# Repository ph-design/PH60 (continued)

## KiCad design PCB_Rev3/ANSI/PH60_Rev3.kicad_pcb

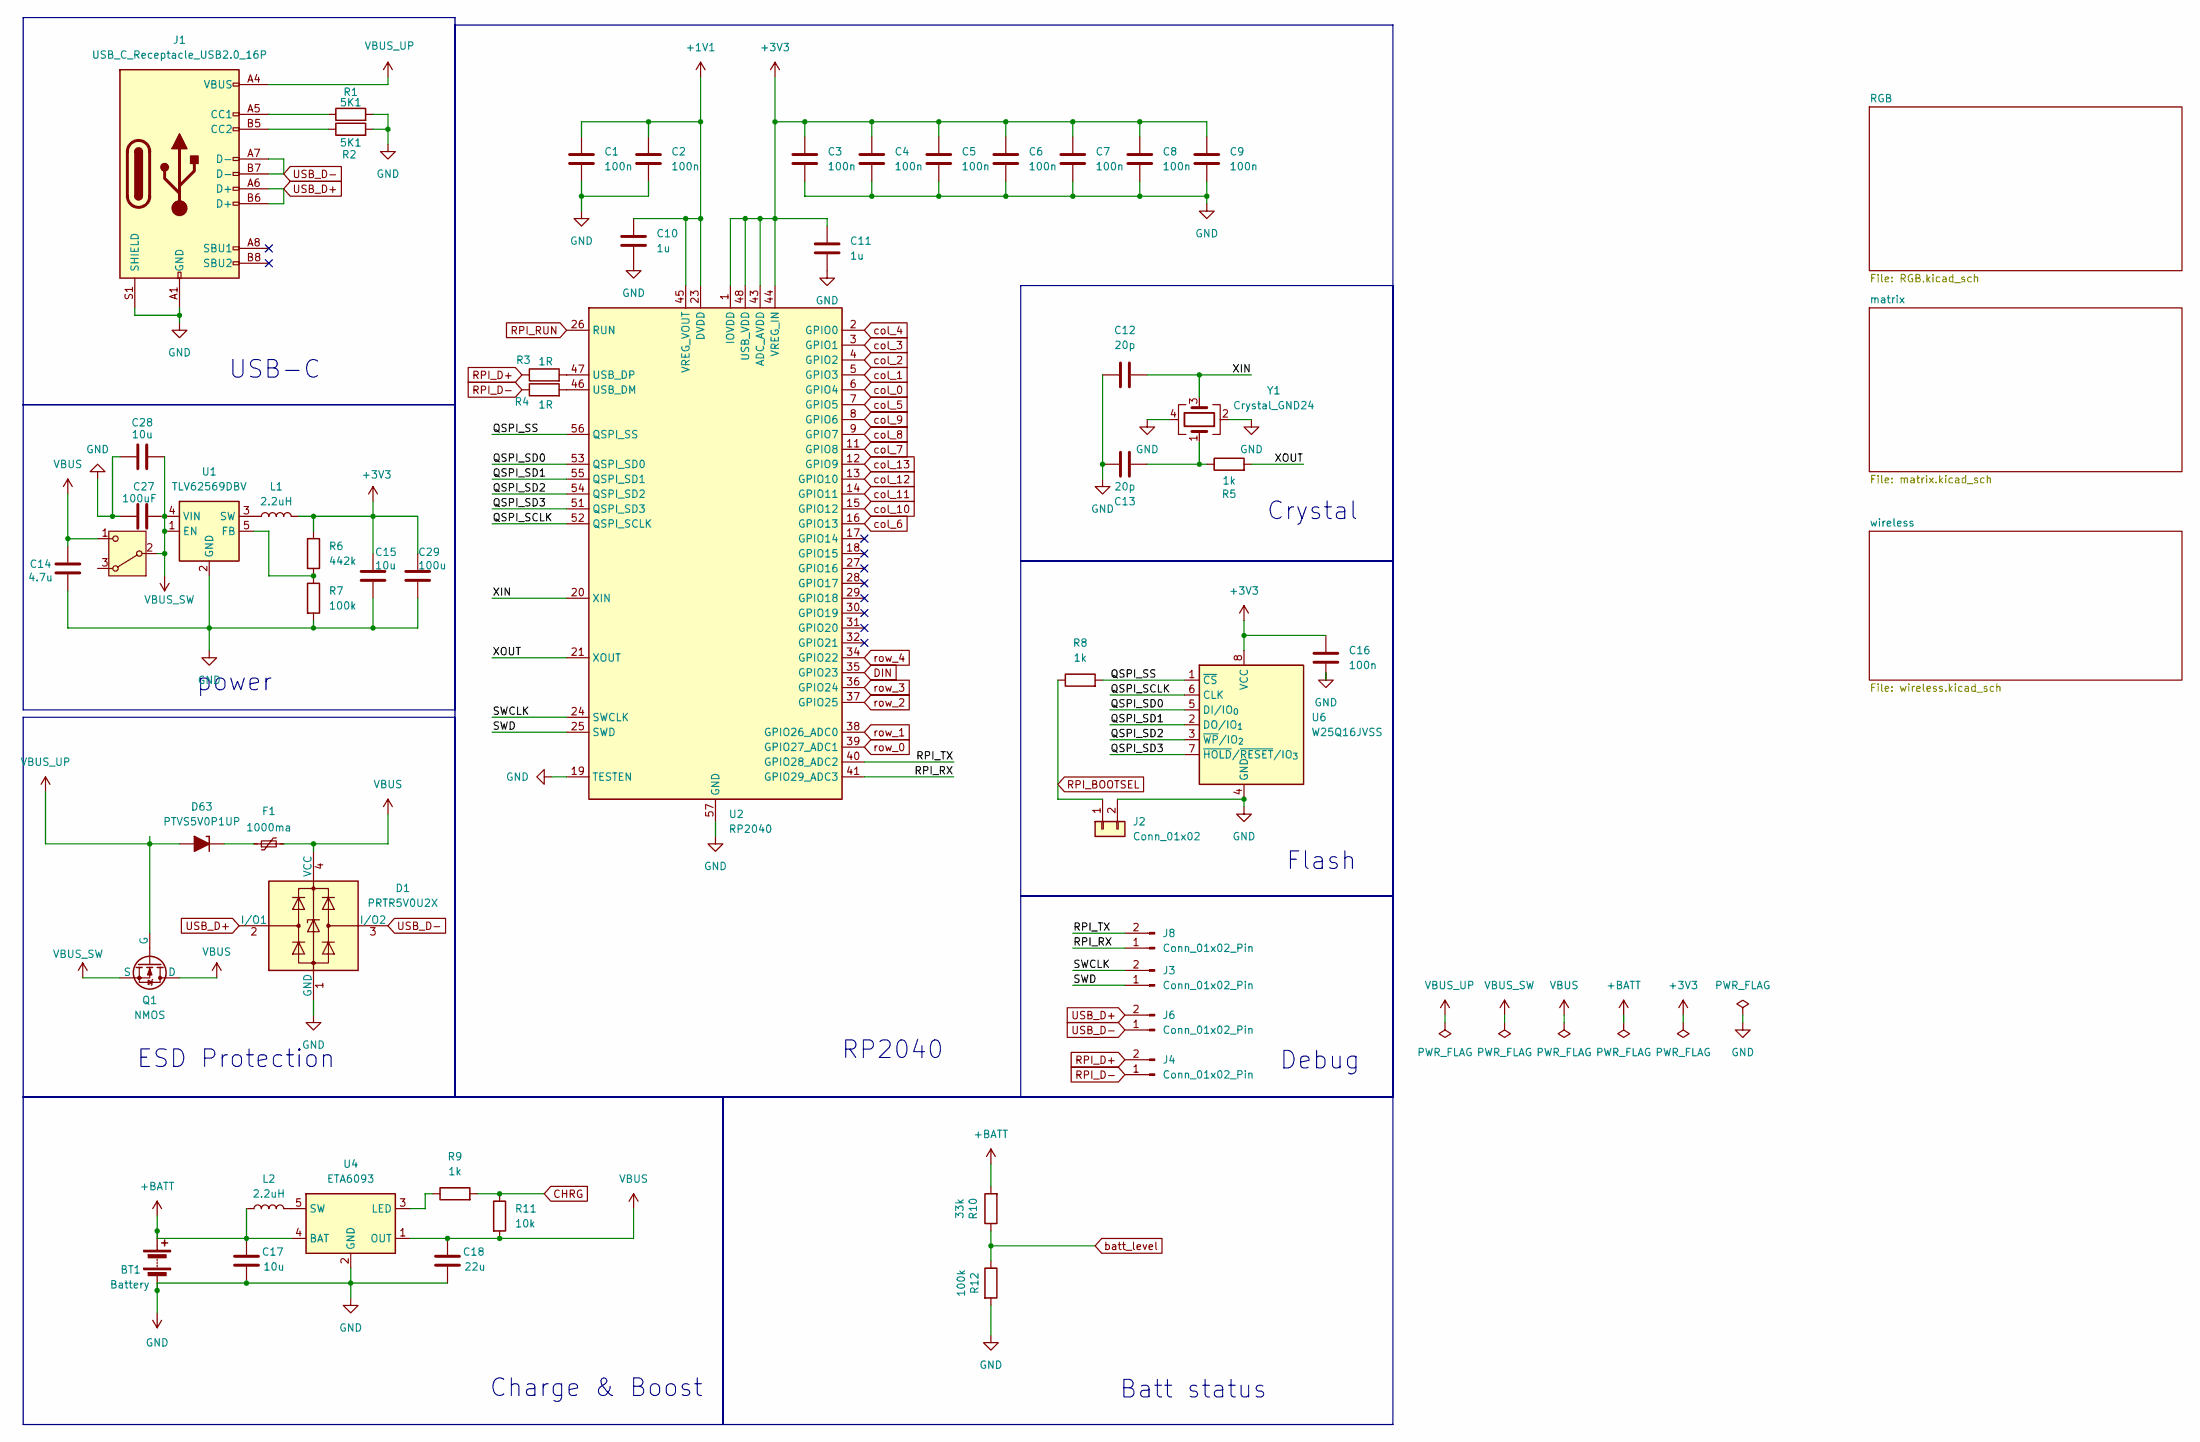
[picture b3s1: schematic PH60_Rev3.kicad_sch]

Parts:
BT1: Battery; Molex_PicoBlade_With_Via
C1, C2, C3, C4, C5, C6, C7, C8, C9, C16: 100n; C_0402_1005Metric
C10, C11: 1u; C_0402_1005Metric
C12, C13: 20p; C_0402_1005Metric
C14: 4.7u; C_0402_1005Metric
C15, C17, C28: 10u; C_0402_1005Metric
C18: 22u; C_0402_1005Metric
C27: 100uF; C_1206_3216Metric
C29: 100u; C_0402_1005Metric
D1: PRTR5V0U2X; SOT-143
D63: PTVS5V0P1UP; D_0603_1608Metric_TVS
F1: 1000ma; Fuse_0805_2012Metric
J1: USB_C_Receptacle_USB2.0_16P; USB-C_16P_HandSolder
J2: Conn_01x02; PinHeader_1x02_P2.54mm_Vertical
J3, J6, J8: Conn_01x02_Pin; PinHeader_1x02_P2.00mm_Vertical
J4: Conn_01x02_Pin; PinHeader_1x02_P1.27mm_Vertical
L1, L2: 2.2uH; L_Changjiang_FNR252012S
Q1: NMOS; SOT-23-3
R1, R2: 5K1; R_0402_1005Metric
R3, R4: 1R; R_0402_1005Metric
R5, R8, R9: 1k; R_0402_1005Metric
R6: 442k; R_0402_1005Metric
R7, R12: 100k; R_0402_1005Metric
R10: 33k; R_0402_1005Metric
R11: 10k; R_0402_1005Metric
SW1: SW_SPDT_321; SW_MSK12C02-HB
U1: TLV62569DBV; SOT-23-5
U2: RP2040; QFN-56-1EP_7x7mm_P0.4mm_EP3.2x3.2mm
U4: ETA6093; SOT-23-5
U6: W25Q16JVSS; Winbond_USON-8-1EP_3x2mm_P0.5mm_EP0.2x1.6mm
Y1: Crystal_GND24; Crystal_SMD_3225-4Pin_3.2x2.5mm

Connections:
+1V1: C1.1, C2.1, C10.1, U2.23 (DVDD), U2.45 (VREG_VOUT), U2.50 (DVDD)
+3V3: C3.1, C4.1, C5.1, C6.1, C7.1, C8.1, C9.1, C11.1, C15.1, C16.1, C29.1, L1.2, R6.1, U2.1 (IOVDD), U2.10 (IOVDD), U2.22 (IOVDD), U2.33 (IOVDD), U2.42 (IOVDD), U2.43 (ADC_AVDD), U2.44 (VREG_IN), U2.48 (USB_VDD), U2.49 (IOVDD), U6.8 (VCC); also elsewhere on the board
+BATT: BT1.1 (+), C17.1, L2.1, R10.2, U4.4 (BAT)
/QSPI_SCLK: U2.52 (QSPI_SCLK), U6.6 (CLK)
/QSPI_SD0: U2.53 (QSPI_SD0), U6.5 (DI/IO_{0})
/QSPI_SD1: U2.55 (QSPI_SD1), U6.2 (DO/IO_{1})
/QSPI_SD2: U2.54 (QSPI_SD2), U6.3 (~WP/IO_{2})
/QSPI_SD3: U2.51 (QSPI_SD3), U6.7 (~HOLD/~RESET/IO_{3})
/QSPI_SS: R8.2, U2.56 (QSPI_SS), U6.1 (~CS)
/RPI_RX: J8.1, U2.41 (GPIO29_ADC3)
/RPI_TX: J8.2, U2.40 (GPIO28_ADC2)
/SWCLK: J3.2, U2.24 (SWCLK)
/SWD: J3.1, U2.25 (SWD)
/XIN: C12.1, U2.20 (XIN), Y1.3
/XOUT: R5.2, U2.21 (XOUT)
CHRG: R9.2, R11.1; also elsewhere on the board
DIN: U2.35 (GPIO23); also elsewhere on the board
GND: BT1.2 (-), C1.2, C2.2, C3.2, C4.2, C5.2, C6.2, C7.2, C8.2, C9.2, C10.2, C11.2, C12.2, C13.2, C14.2, C15.2, C16.2, C17.2, C18.2, C27.1, C28.1, C29.2, D1.1 (GND), J1.A1 (GND), J1.A12 (GND), J1.B1 (GND), J1.B12 (GND), J1.S1 (SHIELD), J2.2, R1.2, R2.2, R7.2, R12.2, U1.2 (GND), U2.19 (TESTEN), U2.57 (GND), U4.2 (GND), U6.4 (GND), Y1.2, Y1.4; also elsewhere on the board
unnamed: C13.1, R5.1, Y1.1
unnamed: D63.1 (K), F1.1
unnamed: J1.A5 (CC1), R1.1
unnamed: J1.B5 (CC2), R2.1
unnamed: R6.2, R7.1, U1.5 (FB)
unnamed: L1.1, U1.3 (SW)
unnamed: R4.2, U2.46 (USB_DM)
unnamed: R3.2, U2.47 (USB_DP)
unnamed: R9.1, U4.3 (LED)
unnamed: L2.2, U4.5 (SW)
RPI_BOOTSEL: J2.1, R8.1; also elsewhere on the board
RPI_D+: J4.2, R3.1; also elsewhere on the board
RPI_D-: J4.1, R4.1; also elsewhere on the board
RPI_RUN: U2.26 (RUN); also elsewhere on the board
USB_D+: D1.2 (I/O1), J1.A6 (D+), J1.B6 (D+), J6.2; also elsewhere on the board
USB_D-: D1.3 (I/O2), J1.A7 (D-), J1.B7 (D-), J6.1; also elsewhere on the board
VBUS: C14.1, C18.1, D1.4 (VCC), F1.2, Q1.1 (D), R11.2, SW1.1 (C), U4.1 (OUT)
VBUS_SW: C27.2, C28.2, Q1.3 (S), SW1.2 (B), U1.1 (EN), U1.4 (VIN); also elsewhere on the board
VBUS_UP: D63.2 (A), J1.A4 (VBUS), J1.A9 (VBUS), J1.B4 (VBUS), J1.B9 (VBUS), Q1.2 (G)
batt_level: R10.1, R12.1; also elsewhere on the board
col_0: U2.6 (GPIO4); also elsewhere on the board
col_1: U2.5 (GPIO3); also elsewhere on the board
col_2: U2.4 (GPIO2); also elsewhere on the board
col_3: U2.3 (GPIO1); also elsewhere on the board
col_4: U2.2 (GPIO0); also elsewhere on the board
col_5: U2.7 (GPIO5); also elsewhere on the board
col_6: U2.16 (GPIO13); also elsewhere on the board
col_7: U2.11 (GPIO8); also elsewhere on the board
col_8: U2.9 (GPIO7); also elsewhere on the board
col_9: U2.8 (GPIO6); also elsewhere on the board
col_10: U2.15 (GPIO12); also elsewhere on the board
col_11: U2.14 (GPIO11); also elsewhere on the board
col_12: U2.13 (GPIO10); also elsewhere on the board
col_13: U2.12 (GPIO9); also elsewhere on the board
row_0: U2.39 (GPIO27_ADC1); also elsewhere on the board
row_1: U2.38 (GPIO26_ADC0); also elsewhere on the board
row_2: U2.37 (GPIO25); also elsewhere on the board
row_3: U2.36 (GPIO24); also elsewhere on the board
row_4: U2.34 (GPIO22); also elsewhere on the board

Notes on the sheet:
Batt status
ESD Protection
Charge & Boost
USB-C
Crystal
Flash
power
RP2040
Debug

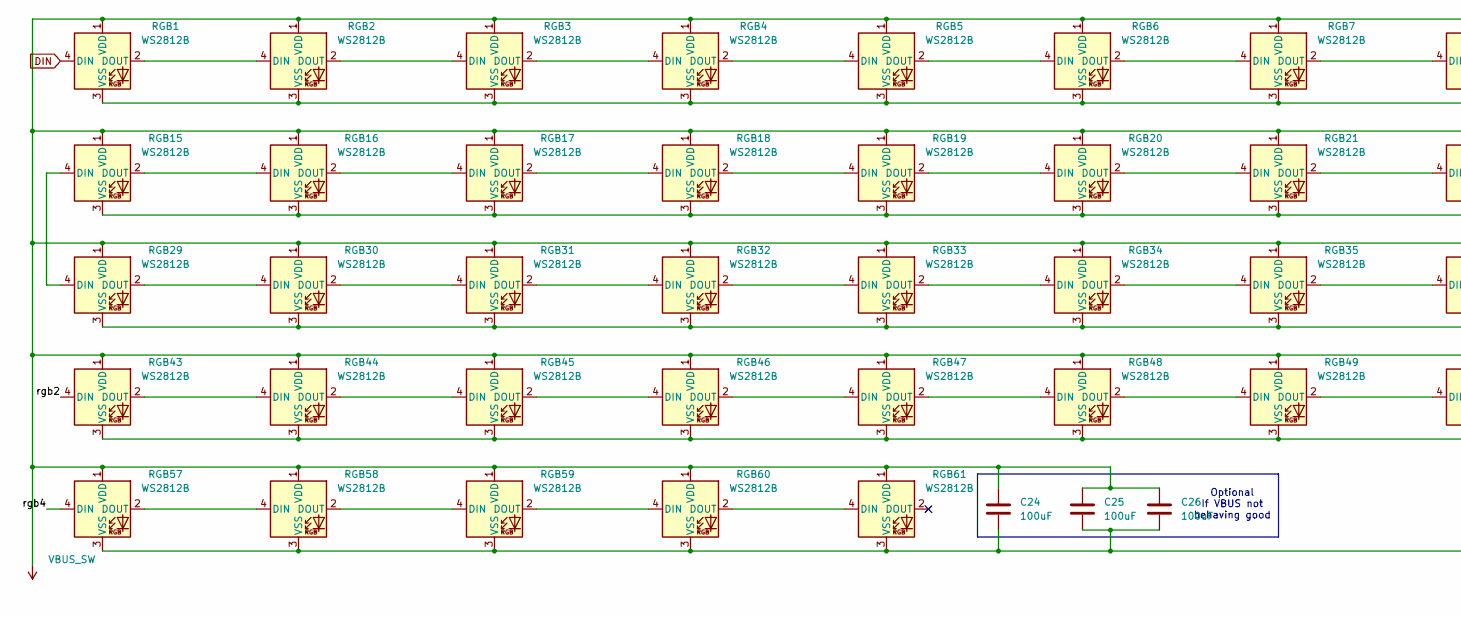
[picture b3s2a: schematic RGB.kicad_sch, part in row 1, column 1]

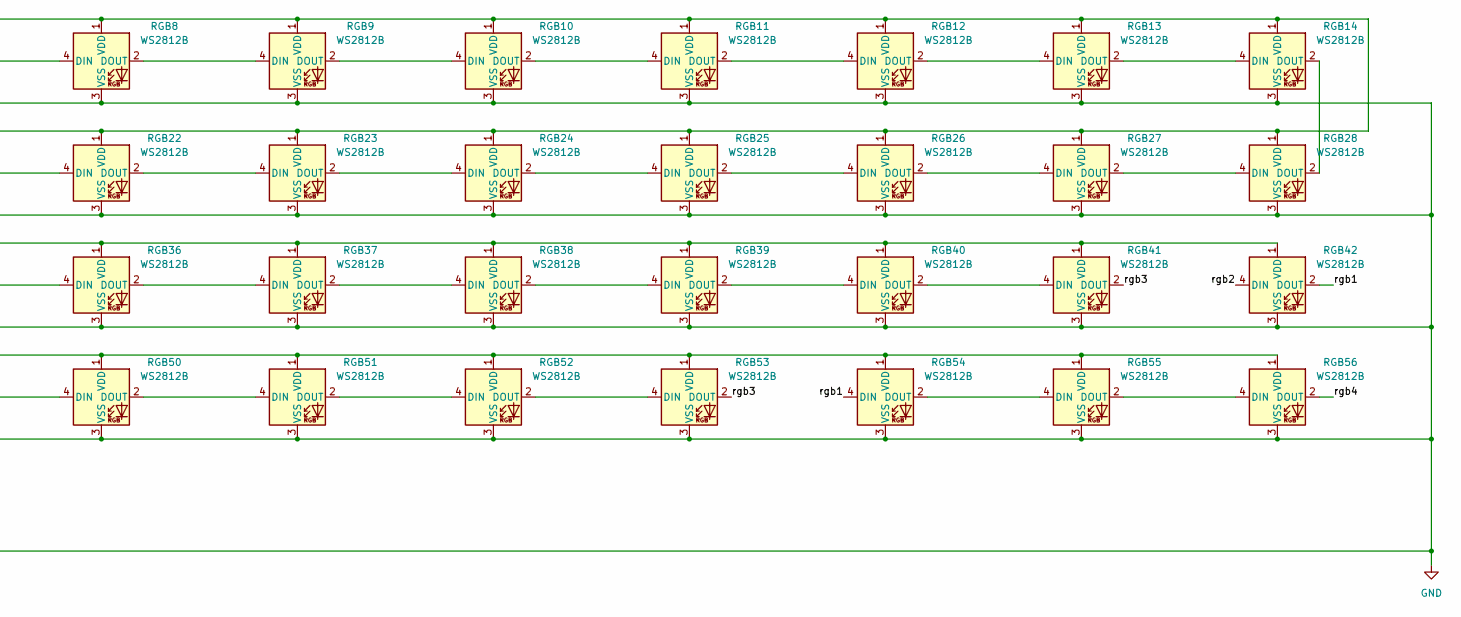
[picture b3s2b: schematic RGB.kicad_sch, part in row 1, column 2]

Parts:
C24, C25, C26: 100uF; C_1206_3216Metric
RGB1, RGB2, RGB3, RGB4, RGB5, RGB6, RGB7, RGB8, RGB9, RGB10, RGB11, RGB12, RGB13, RGB14, RGB15, RGB16, RGB17, RGB18, RGB19, RGB20, RGB21, RGB22, RGB23, RGB24, RGB25, RGB26, RGB27, RGB28, RGB29, RGB30, RGB31, RGB32, RGB33, RGB34, RGB35, RGB36, RGB37, RGB38, RGB39, RGB40, RGB41, RGB42, RGB43, RGB44, RGB45, RGB46, RGB47, RGB48, RGB49, RGB50, RGB51, RGB52, RGB53, RGB54, RGB55, RGB56, RGB57, RGB58, RGB59, RGB60, RGB61: WS2812B; ws2812b_6028

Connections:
/RGB/rgb1: RGB42.2 (DOUT), RGB54.4 (DIN)
/RGB/rgb2: RGB42.4 (DIN), RGB43.4 (DIN)
/RGB/rgb3: RGB41.2 (DOUT), RGB53.2 (DOUT)
/RGB/rgb4: RGB56.2 (DOUT), RGB57.4 (DIN)
DIN: RGB1.4 (DIN); also elsewhere on the board
GND: C24.2, C25.2, C26.2, RGB1.3 (VSS), RGB2.3 (VSS), RGB3.3 (VSS), RGB4.3 (VSS), RGB5.3 (VSS), RGB6.3 (VSS), RGB7.3 (VSS), RGB8.3 (VSS), RGB9.3 (VSS), RGB10.3 (VSS), RGB11.3 (VSS), RGB12.3 (VSS), RGB13.3 (VSS), RGB14.3 (VSS), RGB15.3 (VSS), RGB16.3 (VSS), RGB17.3 (VSS), RGB18.3 (VSS), RGB19.3 (VSS), RGB20.3 (VSS), RGB21.3 (VSS), RGB22.3 (VSS), RGB23.3 (VSS), RGB24.3 (VSS), RGB25.3 (VSS), RGB26.3 (VSS), RGB27.3 (VSS), RGB28.3 (VSS), RGB29.3 (VSS), RGB30.3 (VSS), RGB31.3 (VSS), RGB32.3 (VSS), RGB33.3 (VSS), RGB34.3 (VSS), RGB35.3 (VSS), RGB36.3 (VSS), RGB37.3 (VSS), RGB38.3 (VSS), RGB39.3 (VSS), RGB40.3 (VSS), RGB41.3 (VSS), RGB42.3 (VSS), RGB43.3 (VSS), RGB44.3 (VSS), RGB45.3 (VSS), RGB46.3 (VSS), RGB47.3 (VSS), RGB48.3 (VSS), RGB49.3 (VSS), RGB50.3 (VSS), RGB51.3 (VSS), RGB52.3 (VSS), RGB53.3 (VSS), RGB54.3 (VSS), RGB55.3 (VSS), RGB56.3 (VSS), RGB57.3 (VSS), RGB58.3 (VSS), RGB59.3 (VSS), RGB60.3 (VSS), RGB61.3 (VSS); also elsewhere on the board
unnamed: RGB1.2 (DOUT), RGB2.4 (DIN)
unnamed: RGB2.2 (DOUT), RGB3.4 (DIN)
unnamed: RGB3.2 (DOUT), RGB4.4 (DIN)
unnamed: RGB4.2 (DOUT), RGB5.4 (DIN)
unnamed: RGB5.2 (DOUT), RGB6.4 (DIN)
unnamed: RGB6.2 (DOUT), RGB7.4 (DIN)
unnamed: RGB7.2 (DOUT), RGB8.4 (DIN)
unnamed: RGB8.2 (DOUT), RGB9.4 (DIN)
unnamed: RGB9.2 (DOUT), RGB10.4 (DIN)
unnamed: RGB10.2 (DOUT), RGB11.4 (DIN)
unnamed: RGB11.2 (DOUT), RGB12.4 (DIN)
unnamed: RGB12.2 (DOUT), RGB13.4 (DIN)
unnamed: RGB13.2 (DOUT), RGB14.4 (DIN)
unnamed: RGB14.2 (DOUT), RGB28.2 (DOUT)
unnamed: RGB15.4 (DIN), RGB29.4 (DIN)
unnamed: RGB15.2 (DOUT), RGB16.4 (DIN)
unnamed: RGB16.2 (DOUT), RGB17.4 (DIN)
unnamed: RGB17.2 (DOUT), RGB18.4 (DIN)
unnamed: RGB18.2 (DOUT), RGB19.4 (DIN)
unnamed: RGB19.2 (DOUT), RGB20.4 (DIN)
unnamed: RGB20.2 (DOUT), RGB21.4 (DIN)
unnamed: RGB21.2 (DOUT), RGB22.4 (DIN)
unnamed: RGB22.2 (DOUT), RGB23.4 (DIN)
unnamed: RGB23.2 (DOUT), RGB24.4 (DIN)
unnamed: RGB24.2 (DOUT), RGB25.4 (DIN)
unnamed: RGB25.2 (DOUT), RGB26.4 (DIN)
unnamed: RGB26.2 (DOUT), RGB27.4 (DIN)
unnamed: RGB27.2 (DOUT), RGB28.4 (DIN)
unnamed: RGB29.2 (DOUT), RGB30.4 (DIN)
unnamed: RGB30.2 (DOUT), RGB31.4 (DIN)
unnamed: RGB31.2 (DOUT), RGB32.4 (DIN)
unnamed: RGB32.2 (DOUT), RGB33.4 (DIN)
unnamed: RGB33.2 (DOUT), RGB34.4 (DIN)
unnamed: RGB34.2 (DOUT), RGB35.4 (DIN)
unnamed: RGB35.2 (DOUT), RGB36.4 (DIN)
unnamed: RGB36.2 (DOUT), RGB37.4 (DIN)
unnamed: RGB37.2 (DOUT), RGB38.4 (DIN)
unnamed: RGB38.2 (DOUT), RGB39.4 (DIN)
unnamed: RGB39.2 (DOUT), RGB40.4 (DIN)
unnamed: RGB40.2 (DOUT), RGB41.4 (DIN)
unnamed: RGB43.2 (DOUT), RGB44.4 (DIN)
unnamed: RGB44.2 (DOUT), RGB45.4 (DIN)
unnamed: RGB45.2 (DOUT), RGB46.4 (DIN)
unnamed: RGB46.2 (DOUT), RGB47.4 (DIN)
unnamed: RGB47.2 (DOUT), RGB48.4 (DIN)
unnamed: RGB48.2 (DOUT), RGB49.4 (DIN)
unnamed: RGB49.2 (DOUT), RGB50.4 (DIN)
unnamed: RGB50.2 (DOUT), RGB51.4 (DIN)
unnamed: RGB51.2 (DOUT), RGB52.4 (DIN)
unnamed: RGB52.2 (DOUT), RGB53.4 (DIN)
unnamed: RGB54.2 (DOUT), RGB55.4 (DIN)
unnamed: RGB55.2 (DOUT), RGB56.4 (DIN)
unnamed: RGB57.2 (DOUT), RGB58.4 (DIN)
unnamed: RGB58.2 (DOUT), RGB59.4 (DIN)
unnamed: RGB59.2 (DOUT), RGB60.4 (DIN)
unnamed: RGB60.2 (DOUT), RGB61.4 (DIN)
VBUS_SW: C24.1, C25.1, C26.1, RGB1.1 (VDD), RGB2.1 (VDD), RGB3.1 (VDD), RGB4.1 (VDD), RGB5.1 (VDD), RGB6.1 (VDD), RGB7.1 (VDD), RGB8.1 (VDD), RGB9.1 (VDD), RGB10.1 (VDD), RGB11.1 (VDD), RGB12.1 (VDD), RGB13.1 (VDD), RGB14.1 (VDD), RGB15.1 (VDD), RGB16.1 (VDD), RGB17.1 (VDD), RGB18.1 (VDD), RGB19.1 (VDD), RGB20.1 (VDD), RGB21.1 (VDD), RGB22.1 (VDD), RGB23.1 (VDD), RGB24.1 (VDD), RGB25.1 (VDD), RGB26.1 (VDD), RGB27.1 (VDD), RGB28.1 (VDD), RGB29.1 (VDD), RGB30.1 (VDD), RGB31.1 (VDD), RGB32.1 (VDD), RGB33.1 (VDD), RGB34.1 (VDD), RGB35.1 (VDD), RGB36.1 (VDD), RGB37.1 (VDD), RGB38.1 (VDD), RGB39.1 (VDD), RGB40.1 (VDD), RGB41.1 (VDD), RGB42.1 (VDD), RGB43.1 (VDD), RGB44.1 (VDD), RGB45.1 (VDD), RGB46.1 (VDD), RGB47.1 (VDD), RGB48.1 (VDD), RGB49.1 (VDD), RGB50.1 (VDD), RGB51.1 (VDD), RGB52.1 (VDD), RGB53.1 (VDD), RGB54.1 (VDD), RGB55.1 (VDD), RGB56.1 (VDD), RGB57.1 (VDD), RGB58.1 (VDD), RGB59.1 (VDD), RGB60.1 (VDD), RGB61.1 (VDD); also elsewhere on the board

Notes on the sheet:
Optional If VBUS not behaving good

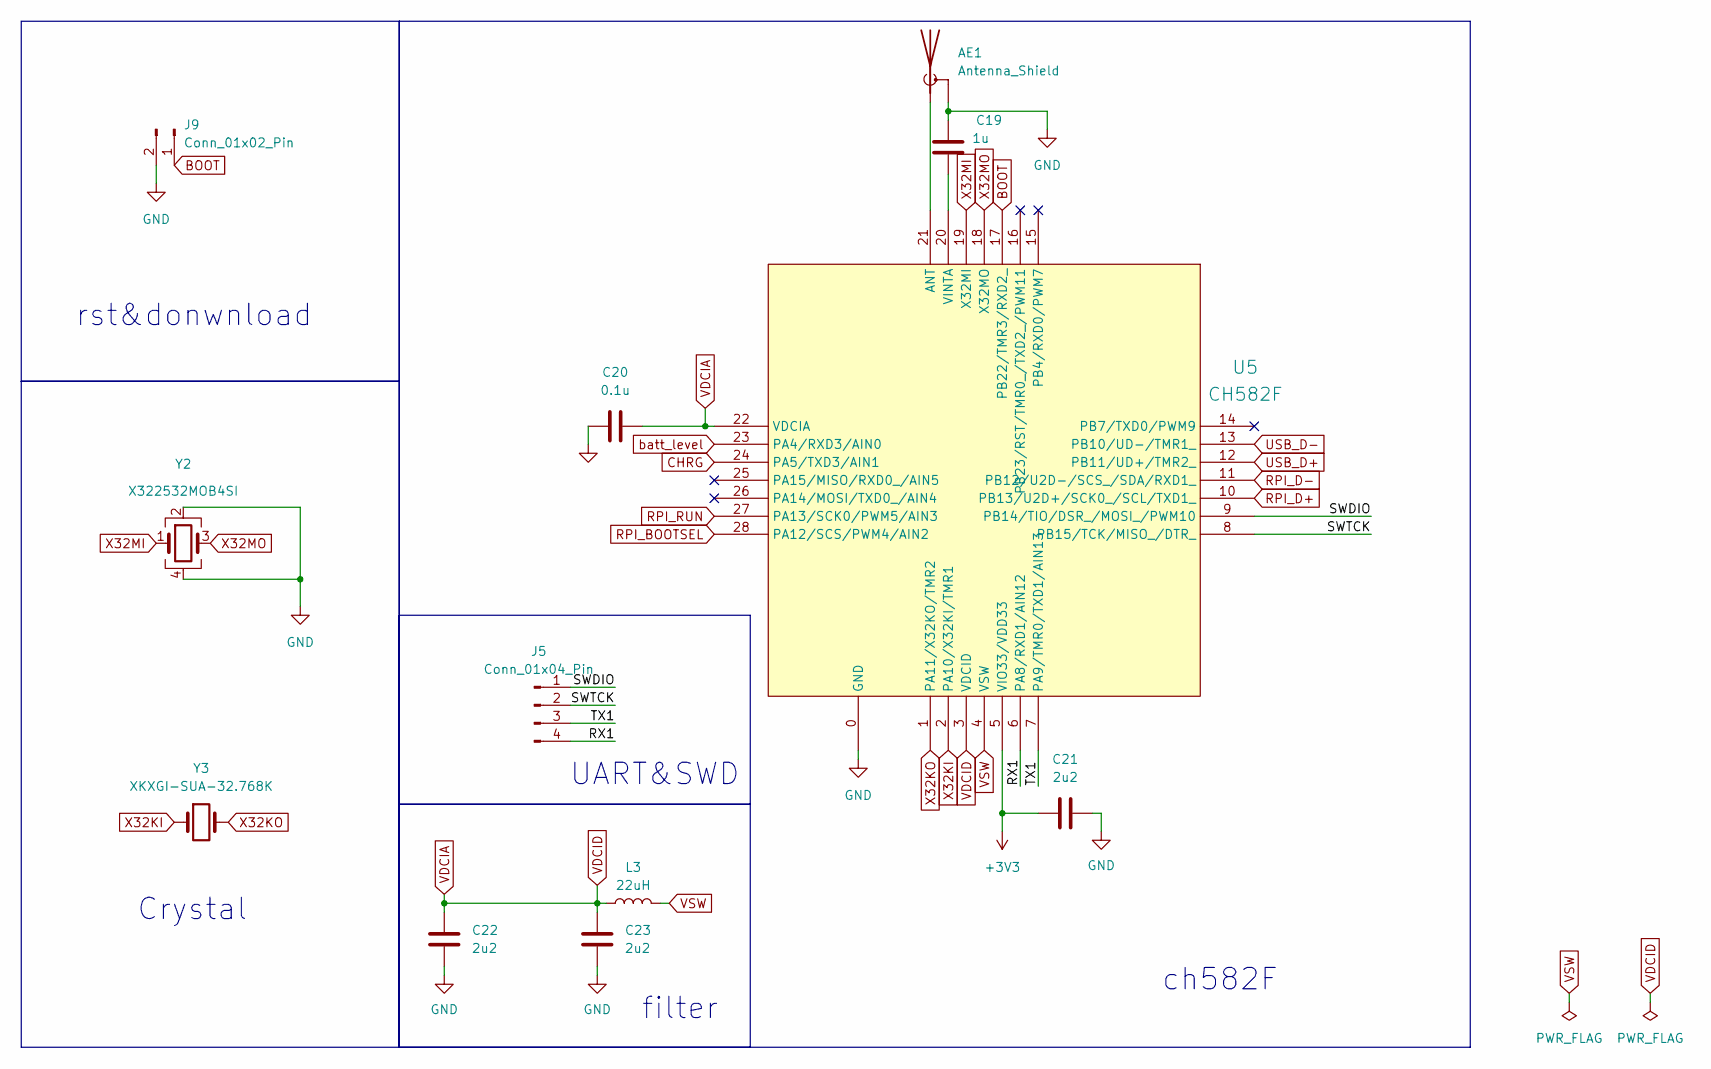
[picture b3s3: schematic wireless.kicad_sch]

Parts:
AE1: Antenna_Shield; ANT-2.4G-1.6MM-MINI-Reversed
C19: 1u; C_0402_1005Metric
C20: 0.1u; C_0402_1005Metric
C21, C22, C23: 2u2; C_0402_1005Metric
J5: Conn_01x04_Pin; PinHeader_1x04_P2.00mm_Vertical
J9: Conn_01x02_Pin; PinHeader_1x02_P2.00mm_Vertical
L3: 22uH; L_Changjiang_FNR252012S
U5: CH582F; QFN28_4X4_FIX
Y2: X322532MOB4SI; Crystal_SMD_3225-4Pin_3.2x2.5mm
Y3: XKXGI-SUA-32.768K; Crystal_SMD_3215-2Pin_3.2x1.5mm

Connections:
+3V3: C21.1, U5.5 (VIO33/VDD33); also elsewhere on the board
/wireless/RX1: J5.4, U5.6 (PA8/RXD1/AIN12)
/wireless/SWDIO: J5.1, U5.9 (PB14/TIO/DSR_/MOSI_/PWM10)
/wireless/SWTCK: J5.2, U5.8 (PB15/TCK/MISO_/DTR_)
/wireless/TX1: J5.3, U5.7 (PA9/TMR0/TXD1/AIN13)
BOOT: J9.1, U5.17 (PB22/TMR3/RXD2_)
CHRG: U5.24 (PA5/TXD3/AIN1); also elsewhere on the board
GND: AE1.2 (Shield), C19.1, C20.1, C21.2, C22.2, C23.2, J9.2, U5.0 (GND), Y2.2, Y2.4; also elsewhere on the board
unnamed: AE1.1 (A), U5.21 (ANT)
unnamed: C19.2, U5.20 (VINTA)
RPI_BOOTSEL: U5.28 (PA12/SCS/PWM4/AIN2); also elsewhere on the board
RPI_D+: U5.10 (PB13/U2D+/SCK0_/SCL/TXD1_); also elsewhere on the board
RPI_D-: U5.11 (PB12/U2D-/SCS_/SDA/RXD1_); also elsewhere on the board
RPI_RUN: U5.27 (PA13/SCK0/PWM5/AIN3); also elsewhere on the board
USB_D+: U5.12 (PB11/UD+/TMR2_); also elsewhere on the board
USB_D-: U5.13 (PB10/UD-/TMR1_); also elsewhere on the board
VDCIA: C20.2, C22.1, C23.1, L3.1, U5.3 (VDCID), U5.22 (VDCIA)
VSW: L3.2, U5.4 (VSW)
X32KI: U5.2 (PA10/X32KI/TMR1), Y3.1
X32KO: U5.1 (PA11/X32KO/TMR2), Y3.2
X32MI: U5.19 (X32MI), Y2.1
X32MO: U5.18 (X32MO), Y2.3
batt_level: U5.23 (PA4/RXD3/AIN0); also elsewhere on the board

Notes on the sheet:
filter
Crystal
rst&donwnload
ch582F
UART&SWD

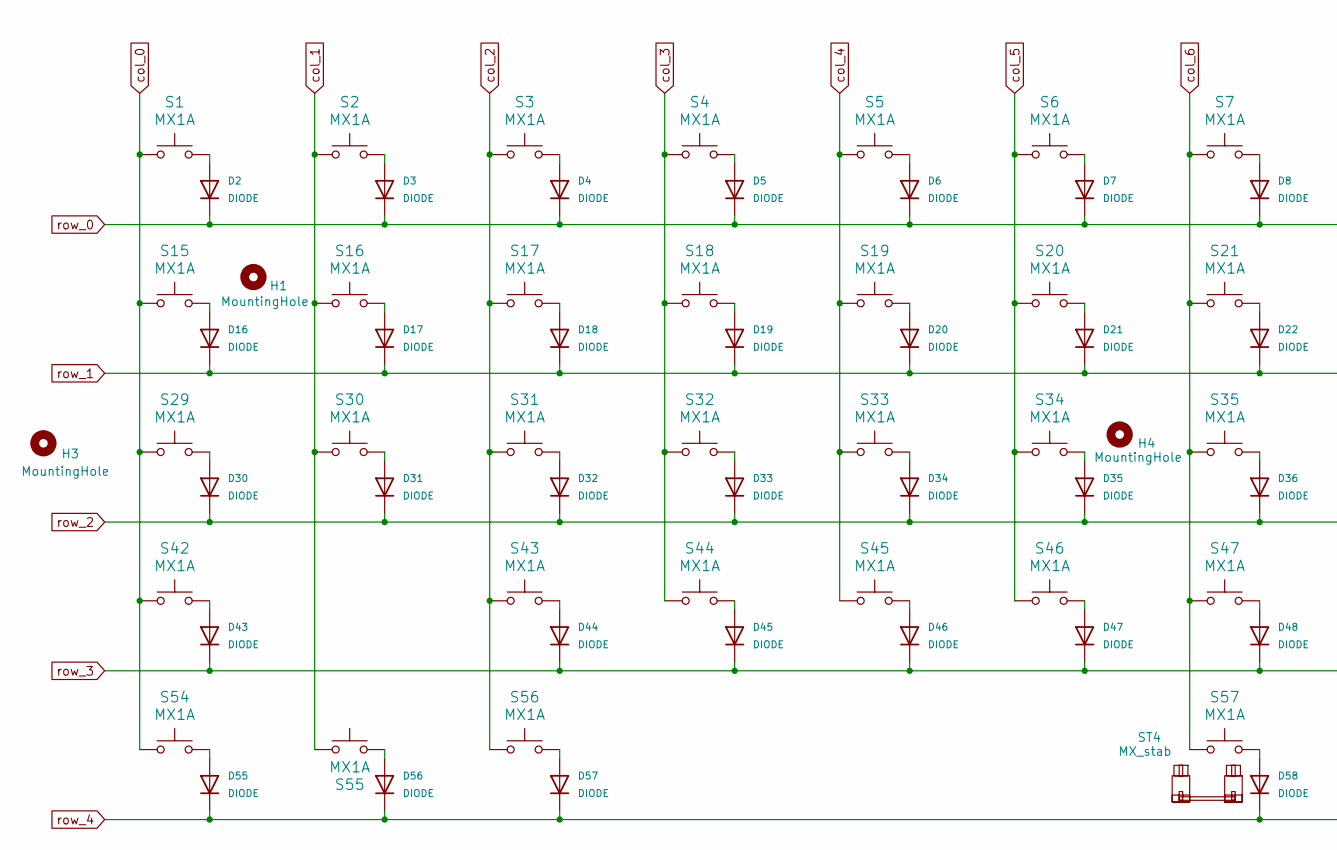
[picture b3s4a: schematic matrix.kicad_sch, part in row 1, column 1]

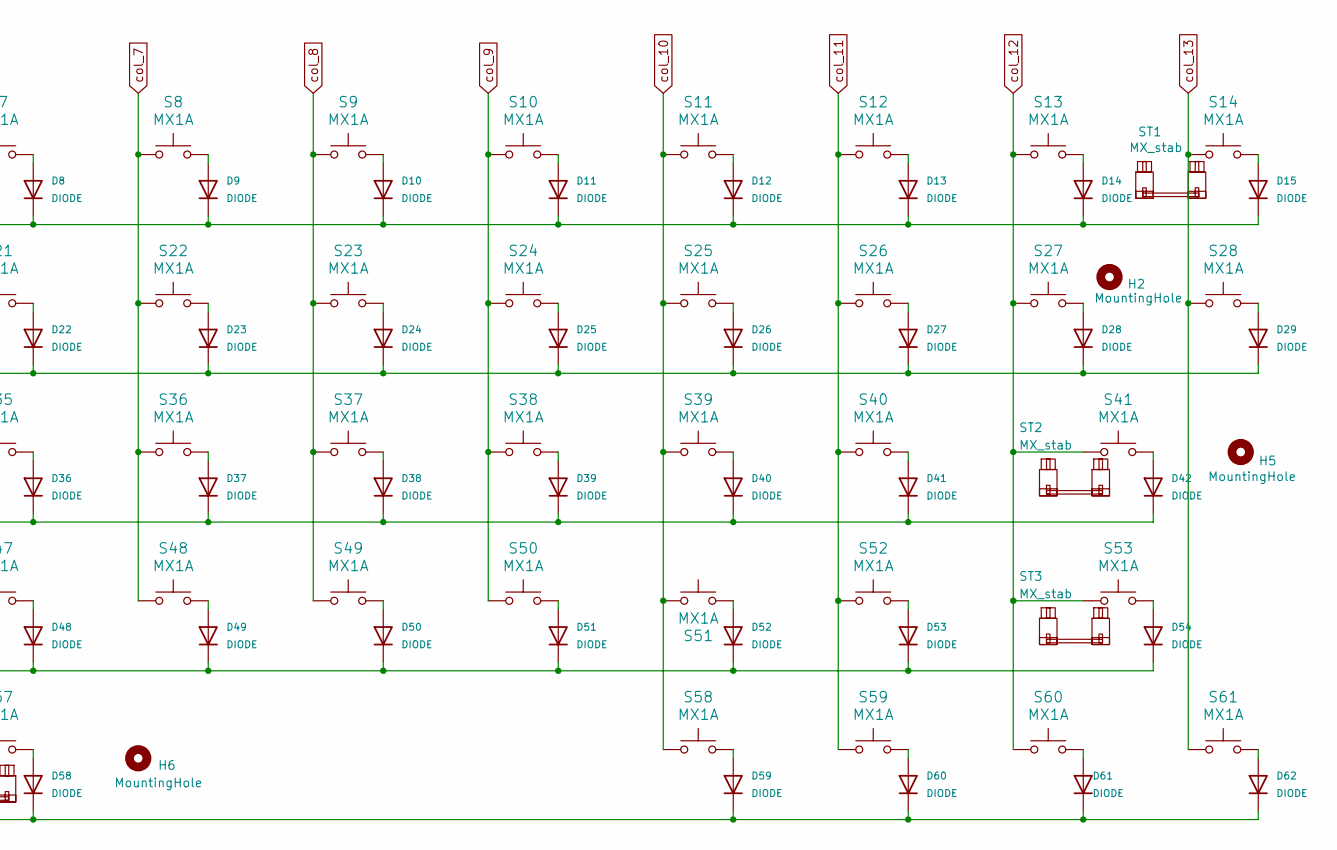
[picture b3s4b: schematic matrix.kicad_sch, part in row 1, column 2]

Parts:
D2, D3, D4, D5, D6, D7, D8, D9, D10, D11, D12, D13, D14, D15, D16, D17, D18, D19, D20, D21, D22, D23, D24, D25, D26, D27, D28, D29, D30, D31, D32, D33, D34, D35, D36, D37, D38, D39, D40, D41, D42, D43, D44, D45, D46, D47, D48, D49, D50, D51, D52, D53, D54, D55, D56, D57, D58, D59, D60, D61, D62: DIODE; D_SOD-323_HandSoldering
H1: MountingHole; PKRHC
H2, H6: MountingHole; PKRH
H3, H5: MountingHole; PKRHSL
H4: MountingHole; PKRHHALF
S1, S2, S3, S4, S5, S6, S7, S8, S9, S10, S11, S12, S13, S16, S17, S18, S19, S20, S21, S22, S23, S24, S25, S26, S27, S30, S31, S32, S33, S34, S35, S36, S37, S38, S39, S40, S43, S44, S45, S46, S47, S48, S49, S50, S51, S52: MX1A; SW_Hotswap_Kailh_MX_Plated_1.00u
S14: MX1A; SW_Hotswap_Kailh_MX_Plated_2.00u
S15, S28: MX1A; SW_Hotswap_Kailh_MX_Plated_1.50u
S29: MX1A; SW_Hotswap_Kailh_MX_Plated_1.75u
S41, S42: MX1A; SW_Hotswap_Kailh_MX_Plated_2.25u
S53: MX1A; SW_Hotswap_Kailh_MX_Plated_2.75u
S54, S55, S56, S58, S59, S60, S61: MX1A; SW_Hotswap_Kailh_MX_Plated_1.25u
S57: MX1A; SW_Hotswap_Kailh_MX_Plated_6.25u
ST1, ST2, ST3: MX_stab; Stabilizer_Cherry_MX_2.00u
ST4: MX_stab; Stabilizer_Cherry_MX_6.25u

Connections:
unnamed: D2.2 (A), S1.1
unnamed: D3.2 (A), S2.1
unnamed: D4.2 (A), S3.1
unnamed: D5.2 (A), S4.1
unnamed: D6.2 (A), S5.1
unnamed: D7.2 (A), S6.1
unnamed: D8.2 (A), S7.1
unnamed: D9.2 (A), S8.1
unnamed: D10.2 (A), S9.1
unnamed: D11.2 (A), S10.1
unnamed: D12.2 (A), S11.1
unnamed: D13.2 (A), S12.1
unnamed: D14.2 (A), S13.1
unnamed: D15.2 (A), S14.1
unnamed: D16.2 (A), S15.1
unnamed: D17.2 (A), S16.1
unnamed: D18.2 (A), S17.1
unnamed: D19.2 (A), S18.1
unnamed: D20.2 (A), S19.1
unnamed: D21.2 (A), S20.1
unnamed: D22.2 (A), S21.1
unnamed: D23.2 (A), S22.1
unnamed: D24.2 (A), S23.1
unnamed: D25.2 (A), S24.1
unnamed: D26.2 (A), S25.1
unnamed: D27.2 (A), S26.1
unnamed: D28.2 (A), S27.1
unnamed: D29.2 (A), S28.1
unnamed: D30.2 (A), S29.1
unnamed: D31.2 (A), S30.1
unnamed: D32.2 (A), S31.1
unnamed: D33.2 (A), S32.1
unnamed: D34.2 (A), S33.1
unnamed: D35.2 (A), S34.1
unnamed: D36.2 (A), S35.1
unnamed: D37.2 (A), S36.1
unnamed: D38.2 (A), S37.1
unnamed: D39.2 (A), S38.1
unnamed: D40.2 (A), S39.1
unnamed: D41.2 (A), S40.1
unnamed: D42.2 (A), S41.1
unnamed: D43.2 (A), S42.1
unnamed: D44.2 (A), S43.1
unnamed: D45.2 (A), S44.1
unnamed: D46.2 (A), S45.1
unnamed: D47.2 (A), S46.1
unnamed: D48.2 (A), S47.1
unnamed: D49.2 (A), S48.1
unnamed: D50.2 (A), S49.1
unnamed: D51.2 (A), S50.1
unnamed: D52.2 (A), S51.1
unnamed: D53.2 (A), S52.1
unnamed: D54.2 (A), S53.1
unnamed: D55.2 (A), S54.1
unnamed: D56.2 (A), S55.1
unnamed: D57.2 (A), S56.1
unnamed: D58.2 (A), S57.1
unnamed: D59.2 (A), S58.1
unnamed: D60.2 (A), S59.1
unnamed: D61.2 (A), S60.1
unnamed: D62.2 (A), S61.1
col_0: S1.2, S15.2, S29.2, S42.2, S54.2; also elsewhere on the board
col_1: S2.2, S16.2, S30.2, S55.2; also elsewhere on the board
col_2: S3.2, S17.2, S31.2, S43.2, S56.2; also elsewhere on the board
col_3: S4.2, S18.2, S32.2, S44.2; also elsewhere on the board
col_4: S5.2, S19.2, S33.2, S45.2; also elsewhere on the board
col_5: S6.2, S20.2, S34.2, S46.2; also elsewhere on the board
col_6: S7.2, S21.2, S35.2, S47.2, S57.2; also elsewhere on the board
col_7: S8.2, S22.2, S36.2, S48.2; also elsewhere on the board
col_8: S9.2, S23.2, S37.2, S49.2; also elsewhere on the board
col_9: S10.2, S24.2, S38.2, S50.2; also elsewhere on the board
col_10: S11.2, S25.2, S39.2, S51.2, S58.2; also elsewhere on the board
col_11: S12.2, S26.2, S40.2, S52.2, S59.2; also elsewhere on the board
col_12: S13.2, S27.2, S41.2, S53.2, S60.2; also elsewhere on the board
col_13: S14.2, S28.2, S61.2; also elsewhere on the board
row_0: D2.1 (K), D3.1 (K), D4.1 (K), D5.1 (K), D6.1 (K), D7.1 (K), D8.1 (K), D9.1 (K), D10.1 (K), D11.1 (K), D12.1 (K), D13.1 (K), D14.1 (K), D15.1 (K); also elsewhere on the board
row_1: D16.1 (K), D17.1 (K), D18.1 (K), D19.1 (K), D20.1 (K), D21.1 (K), D22.1 (K), D23.1 (K), D24.1 (K), D25.1 (K), D26.1 (K), D27.1 (K), D28.1 (K), D29.1 (K); also elsewhere on the board
row_2: D30.1 (K), D31.1 (K), D32.1 (K), D33.1 (K), D34.1 (K), D35.1 (K), D36.1 (K), D37.1 (K), D38.1 (K), D39.1 (K), D40.1 (K), D41.1 (K), D42.1 (K); also elsewhere on the board
row_3: D43.1 (K), D44.1 (K), D45.1 (K), D46.1 (K), D47.1 (K), D48.1 (K), D49.1 (K), D50.1 (K), D51.1 (K), D52.1 (K), D53.1 (K), D54.1 (K); also elsewhere on the board
row_4: D55.1 (K), D56.1 (K), D57.1 (K), D58.1 (K), D59.1 (K), D60.1 (K), D61.1 (K), D62.1 (K); also elsewhere on the board

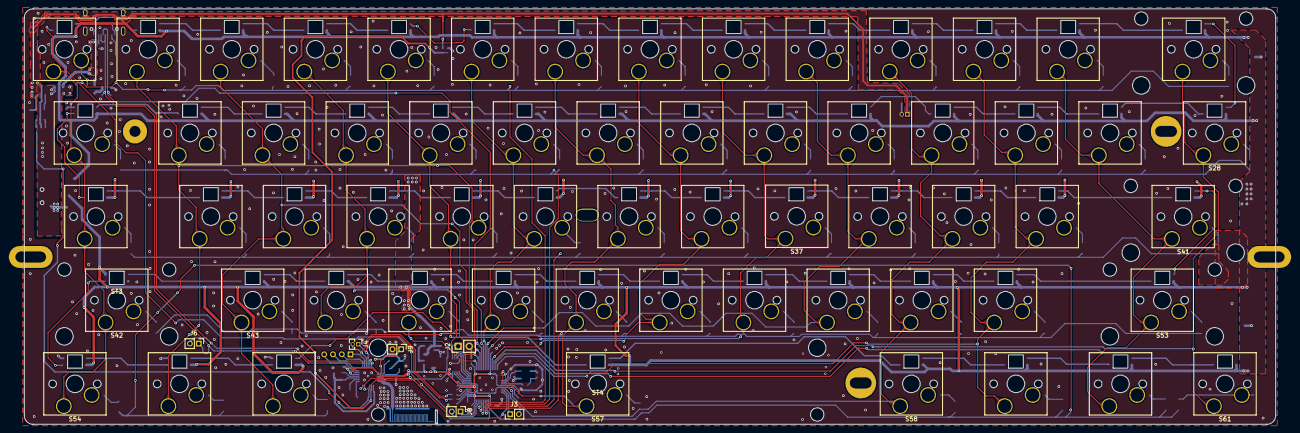
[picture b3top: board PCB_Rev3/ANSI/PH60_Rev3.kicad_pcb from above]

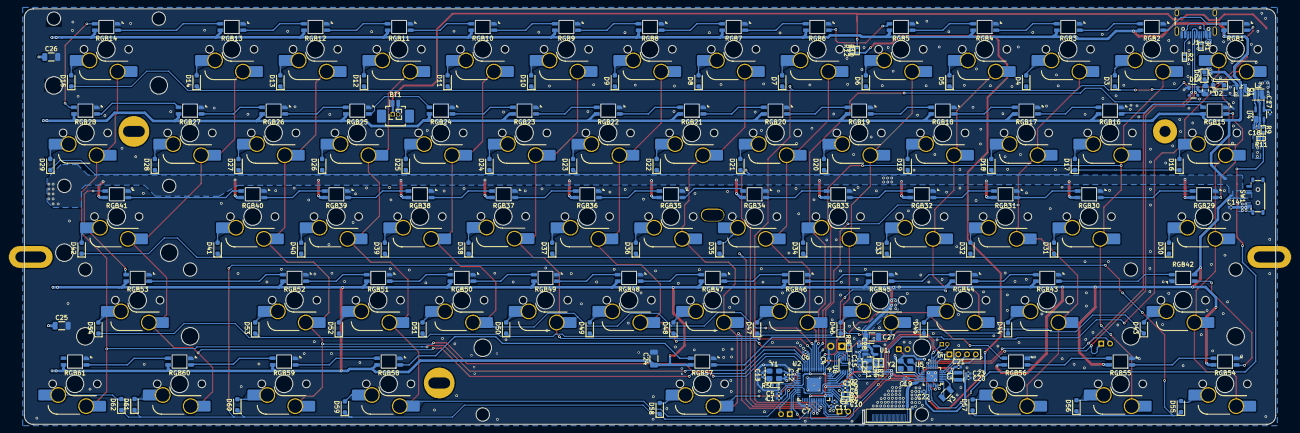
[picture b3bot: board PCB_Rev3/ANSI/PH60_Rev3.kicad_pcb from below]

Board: 2 copper layers, 285.0 x 94.6 mm, 261 parts (183 on the bottom side), 191 nets.

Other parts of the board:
ST0: Stabilizer_Cherry_MX_2.00u
